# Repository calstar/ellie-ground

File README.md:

# ellie-ground
2022 Eillie Hot-fire Electronics Control

## Summary
**DAQboard.ino** file commands the ESP32 that reads data from sensors and commands from the COM Board, and sends data in a package to the COM Board.

**COMBoard.ino** file commands the ESP32 that receives data in a package from the DAQ  Board, sends commands to the DAQ Board, and sends data to MATLAB for plotting and data-saving purposes through the serial port.

**liveplot.m** is a MATLAB file that can receive data from the COM Board, create live plots, and save the data.
  1. **Change the test file name according to the trial number in the liveplot.m file.**
  2. Click "Run" to start the code, and close the plotting window to stop the code. Test data will be automatically stored in a spreadsheet under a folder called "**Test_Data_yyyy-mm-dd**."

## ESP32 MAC Addresses
- DAQ Breadboard:{0x24, 0x62, 0xAB, 0xD2, 0x85, 0xDC}
- COM Breadboard:{0xC4, 0xDD, 0x57, 0x9E, 0x91, 0x6C};
- DAQ Protoboard:

## ESP32 Pinouts (Updated 4/6)
-DAQ Breadboard:

## Software requirement
**Ctrl click (Windows) or Cmd click the following links to open them in new tabs**
1. Arduino (https://www.arduino.cc/en/software)
2. MATLAB (https://software.berkeley.edu/matlab®)
    - To control the serial port, you need to install the [**Instrument Control Toolbox**](https://www.mathworks.com/products/instrument.html).
3. (optional) An external code editing software such as Atom (https://atom.io) or Visual Studio (https://visualstudio.microsoft.com/downloads/).
    - Arduino IDE and MATLAB are sufficient for all the coding
4. (recommended) GitHub Desktop (https://desktop.github.com). You can pull, push, and edit files with ease. **Step 3 required if you would like to download GitHub Desktop as the software requires an external editor.**

## How to update
### Using Github Desktop
1. Make sure you have access to this project
    - Check with you administrators
2. Go to the Github app, sign in, and click on the top left corner. You should see a pop-up window with an "Add" button. Select that button and choose "Clone repository."
3. Search in "Filter you repositories" using the keyword "ellie-ground." Select the correct repository and click "Clone."
    - If you want this cloned repository to be in a different folder, change the "Local Path."
4. After you have edited and saved the file in the local repository, GitHub Desktop will detect changes and prompt you to commit. Make sure to double check your changes before committing.
5. On the bottom left corner, put down a short summary that describes what you have changed, then click "Commit to **main**."
6. In the middle of the screen (or on the top banner) you will see "Push commits to the origin remote." If you are sure that the commit is ready, click "Push origin."
6. Check the project online and see if the changes have been reflected.

### Using Git
Please refer to https://rocketry.gitbook.io/public/tutorials/avionics/git-and-workflow for more information.

## Helpful resources
### ESP32-DevkitC (for PCB application - antenna sticks out of board)
Getting started

https://docs.espressif.com/projects/esp-idf/en/latest/esp32/hw-reference/esp32/get-started-devkitc.html

Pinout reference

### ESP32-WROOM (for breadboard/protoboard application - antenna does NOT stick out of board)

Pinout reference

### ESP32-HUZZAH (for breadboard/protoboard application)

Pinout reference

### Pressure transducer color code
Red - E+

Black - E-

Green - A-

White - A+

Other possible combinations: Blue E+; Red E-; Green A-; Black A+

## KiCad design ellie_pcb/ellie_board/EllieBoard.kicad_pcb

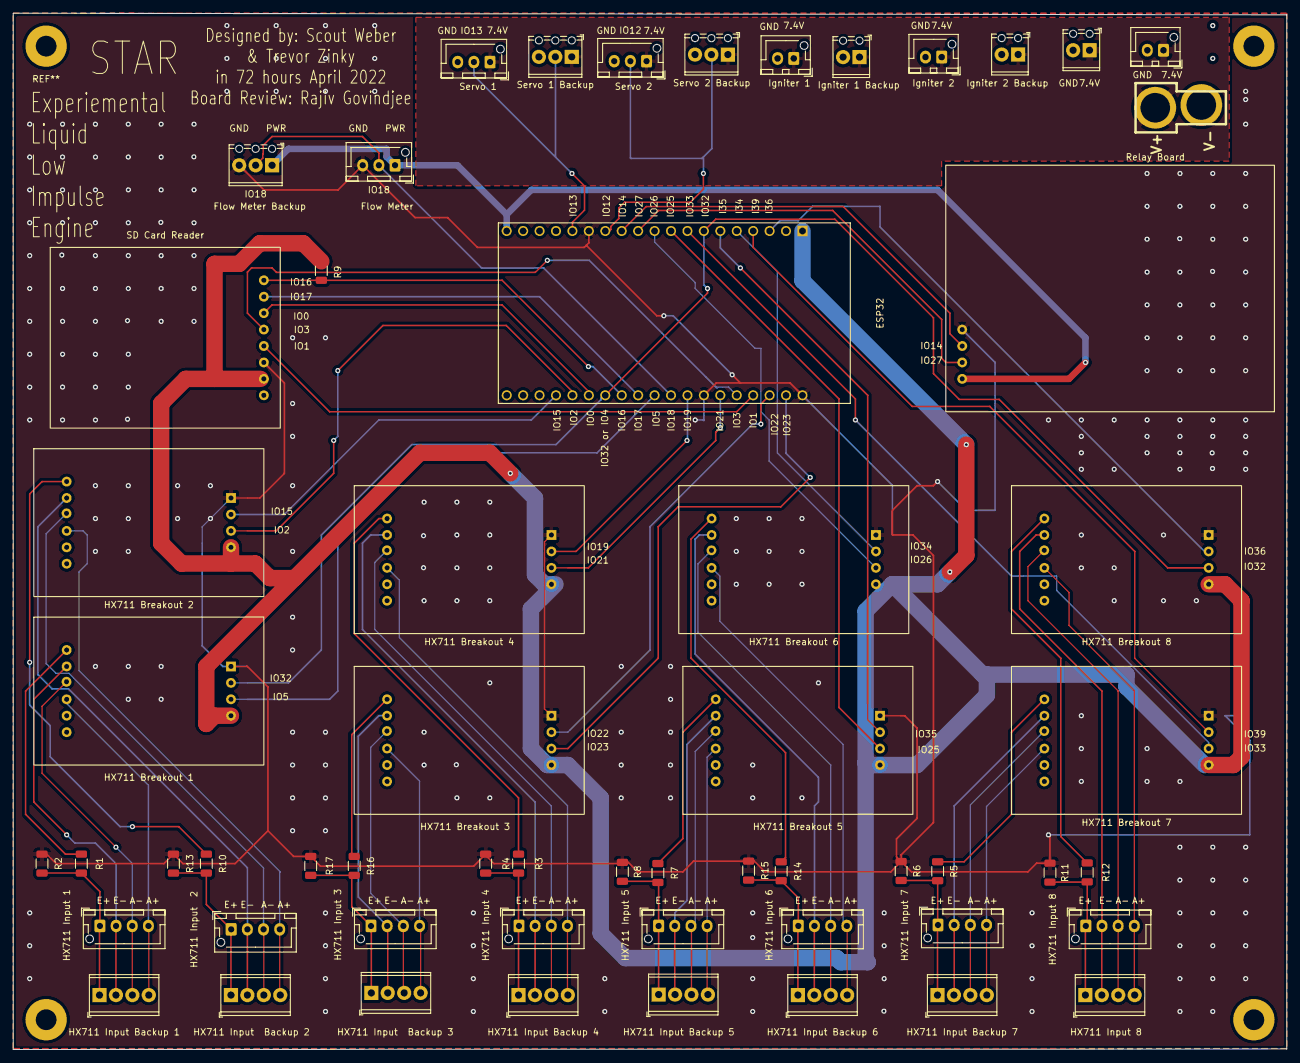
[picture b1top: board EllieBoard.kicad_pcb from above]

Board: 2 copper layers, 196.8 x 160.2 mm, 57 parts (0 on the bottom side), 69 nets.

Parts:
ESP32: ESP32-DEVKITC-32D; MODULE_ESP32-DEVKITC-32D
Flow Meter : Flow Meter Conn 1; JST_XH_B3B-XH-AM_1x03_P2.50mm_Vertical
Flow Meter Backup: Flow Meter Conn 2; TerminalBlock_Phoenix_MPT-0,5-3-2.54_1x03_P2.54mm_Horizontal
HX711 Breakout 1: HX711 Breakout 5; HX711_Breakout_Board
HX711 Breakout 2, HX711 Breakout 4, HX711 Breakout 6, HX711 Breakout 8: HX711_Breakout; HX711_Breakout_Board
HX711 Breakout 3: HX711 Breakout 6; HX711_Breakout_Board
HX711 Breakout 5: HX711 Breakout 7; HX711_Breakout_Board
HX711 Breakout 7: HX711 Breakout 8; HX711_Breakout_Board
HX711 Input 1: Load Cell 1.1; JST_XH_B4B-XH-AM_1x04_P2.50mm_Vertical
HX711 Input 3: Load Cell 3.1; JST_XH_B4B-XH-AM_1x04_P2.50mm_Vertical
HX711 Input 4: Load Cell 4.1; JST_XH_B4B-XH-AM_1x04_P2.50mm_Vertical
HX711 Input 5: Load Cell 5.1; JST_XH_B4B-XH-AM_1x04_P2.50mm_Vertical
HX711 Input 6: Load Cell 6.1; JST_XH_B4B-XH-AM_1x04_P2.50mm_Vertical
HX711 Input 7: Load Cell 7.1; JST_XH_B4B-XH-AM_1x04_P2.50mm_Vertical
HX711 Input 8: Load Cell 8.1; JST_XH_B4B-XH-AM_1x04_P2.50mm_Vertical
HX711 Input 8#2: Load Cell 8.2; TerminalBlock_Phoenix_MPT-0,5-4-2.54_1x04_P2.54mm_Horizontal
HX711 Input  2: Load Cell 2.1; JST_XH_B4B-XH-AM_1x04_P2.50mm_Vertical
HX711 Input  Backup 2: Load Cell 2.2; TerminalBlock_Phoenix_MPT-0,5-4-2.54_1x04_P2.54mm_Horizontal
HX711 Input  Backup 3: Load Cell 3.2; TerminalBlock_Phoenix_MPT-0,5-4-2.54_1x04_P2.54mm_Horizontal
HX711 Input Backup 1: Load Cell 1.2; TerminalBlock_Phoenix_MPT-0,5-4-2.54_1x04_P2.54mm_Horizontal
HX711 Input Backup 4: Load Cell 4.2; TerminalBlock_Phoenix_MPT-0,5-4-2.54_1x04_P2.54mm_Horizontal
HX711 Input Backup 5: Load Cell 5.2; TerminalBlock_Phoenix_MPT-0,5-4-2.54_1x04_P2.54mm_Horizontal
HX711 Input Backup 6: Load Cell 6.2; TerminalBlock_Phoenix_MPT-0,5-4-2.54_1x04_P2.54mm_Horizontal
HX711 Input Backup 7: Load Cell 7.2; TerminalBlock_Phoenix_MPT-0,5-4-2.54_1x04_P2.54mm_Horizontal
Igniter 1 , Igniter 2 : NC Conn; JST_XH_B2B-XH-AM_1x02_P2.50mm_Vertical
Igniter 1 Backup: Igniter 1; TerminalBlock_Phoenix_MPT-0,5-2-2.54_1x02_P2.54mm_Horizontal
Igniter 2 Backup: NC Conn 2; TerminalBlock_Phoenix_MPT-0,5-2-2.54_1x02_P2.54mm_Horizontal
J9: Battery Conn; DEANS
J10: Battery Conn Backup; JST_XH_B2B-XH-AM_1x02_P2.50mm_Vertical
J11: Battery Conn Backup 2; TerminalBlock_Phoenix_MPT-0,5-2-2.54_1x02_P2.54mm_Horizontal
R1, R3, R5, R7, R10, R12, R14, R16: 820; R_1206_3216Metric
R2, R4, R6, R8, R11, R13, R15, R17: 470; R_1206_3216Metric
R9: 10k; R_1206_3216Metric
Relay Board: Relay_Board; Relay_Breakout
SD Card Reader: SD_Card_Reader; SD_Card_Breakout
Servo 1 : Servo Conn 3; JST_XH_B3B-XH-AM_1x03_P2.50mm_Vertical
Servo 1 Backup: Servo Conn 4; TerminalBlock_Phoenix_MPT-0,5-3-2.54_1x03_P2.54mm_Horizontal
Servo 2 : Servo Conn 1; JST_XH_B3B-XH-AM_1x03_P2.50mm_Vertical
Servo 2 Backup: Servo Conn 2; TerminalBlock_Phoenix_MPT-0,5-3-2.54_1x03_P2.54mm_Horizontal

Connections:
+3V3: ESP32.1 (3V3), HX711 Breakout 1.10 (VCC), HX711 Breakout 2.10 (VCC), HX711 Breakout 3.10 (VCC), HX711 Breakout 4.10 (VCC), HX711 Breakout 5.10 (VCC), HX711 Breakout 6.10 (VCC), HX711 Breakout 7.10 (VCC), HX711 Breakout 8.10 (VCC), R9.1, SD Card Reader.7 (3V)
+5V: ESP32.19 (EXT_5V), Flow Meter.1, Flow Meter Backup.1, Relay Board.1 (VCC)
A1+: HX711 Breakout 1.4 (A+), HX711 Input 1.4, HX711 Input Backup 1.4
A1-: HX711 Breakout 1.3 (A-), HX711 Input 1.3, HX711 Input Backup 1.3
A2+: HX711 Breakout 2.4 (A+), HX711 Input 2.4, HX711 Input Backup 2.4
A2-: HX711 Breakout 2.3 (A-), HX711 Input 2.3, HX711 Input Backup 2.3
A3+: HX711 Breakout 3.4 (A+), HX711 Input 3.4, HX711 Input Backup 3.4
A3-: HX711 Breakout 3.3 (A-), HX711 Input 3.3, HX711 Input Backup 3.3
A4+: HX711 Breakout 4.4 (A+), HX711 Input 4.4, HX711 Input Backup 4.4
A4-: HX711 Breakout 4.3 (A-), HX711 Input 4.3, HX711 Input Backup 4.3
A5+: HX711 Breakout 5.4 (A+), HX711 Input 5.4, HX711 Input Backup 5.4
A5-: HX711 Breakout 5.3 (A-), HX711 Input 5.3, HX711 Input Backup 5.3
A6+: HX711 Breakout 6.4 (A+), HX711 Input 6.4, HX711 Input Backup 6.4
A6-: HX711 Breakout 6.3 (A-), HX711 Input 6.3, HX711 Input Backup 6.3
A7+: HX711 Breakout 7.4 (A+), HX711 Input 7.4, HX711 Input Backup 7.4
A7-: HX711 Breakout 7.3 (A-), HX711 Input 7.3, HX711 Input Backup 7.3
A8+: HX711 Breakout 8.4 (A+), HX711 Input 8.4, HX711 Input 8#2.4
A8-: HX711 Breakout 8.3 (A-), HX711 Input 8.3, HX711 Input 8#2.3
GND: ESP32.14 (GND1), ESP32.20 (GND3), ESP32.26 (GND2), Flow Meter.3, Flow Meter Backup.3, HX711 Breakout 1.7 (GND), HX711 Breakout 2.7 (GND), HX711 Breakout 3.7 (GND), HX711 Breakout 4.7 (GND), HX711 Breakout 5.7 (GND), HX711 Breakout 6.7 (GND), HX711 Breakout 7.7 (GND), HX711 Breakout 8.7 (GND), Igniter 1.2, Igniter 1 Backup.2, Igniter 2.2, Igniter 2 Backup.2, J9.2, J10.2, J11.2, R2.1, R4.1, R6.1, R8.1, R11.1, R13.1, R15.1, R17.1, Relay Board.4 (GND), SD Card Reader.6 (GND), Servo 1.3, Servo 1 Backup.3, Servo 2.3, Servo 2 Backup.3
IO2: ESP32.34 (IO2), HX711 Breakout 2.9 (SCK)
IO5: ESP32.29 (IO5), HX711 Breakout 1.9 (SCK)
IO12: ESP32.13 (IO12), Servo 2.2, Servo 2 Backup.2
IO13: ESP32.15 (IO13), Servo 1.2, Servo 1 Backup.2
IO14: ESP32.12 (IO14), Relay Board.3 (IN2)
IO15: ESP32.35 (IO15), HX711 Breakout 2.8 (DT)
IO16: ESP32.31 (IO16), R9.2, SD Card Reader.1 (CD)
IO17: ESP32.30 (IO17), SD Card Reader.2 (CS)
IO18: ESP32.28 (IO18), Flow Meter.2, Flow Meter Backup.2
IO19: ESP32.27 (IO19), HX711 Breakout 4.8 (DT)
IO21: ESP32.25 (IO21), HX711 Breakout 4.9 (SCK)
IO22: ESP32.22 (IO22), HX711 Breakout 3.8 (DT)
IO23: ESP32.21 (IO23), HX711 Breakout 3.9 (SCK)
IO25: ESP32.9 (IO25), HX711 Breakout 5.9 (SCK)
IO26: ESP32.10 (IO26), HX711 Breakout 6.9 (SCK)
IO27: ESP32.11 (IO27), Relay Board.2 (IN1)
IO32: ESP32.7 (IO32), ESP32.32 (IO4), HX711 Breakout 1.8 (DT), HX711 Breakout 8.9 (SCK)
IO33: ESP32.8 (IO33), HX711 Breakout 7.9 (SCK)
IO34: ESP32.5 (IO34), HX711 Breakout 6.8 (DT)
IO35: ESP32.6 (IO35), HX711 Breakout 5.8 (DT)
IO36: ESP32.3 (SENSOR_VP), HX711 Breakout 8.8 (DT)
IO39: ESP32.4 (SENSOR_VN), HX711 Breakout 7.8 (DT)
Lipo: Igniter 1.1, Igniter 1 Backup.1, Igniter 2.1, Igniter 2 Backup.1, J9.1, J10.1, J11.1, Servo 1.1, Servo 1 Backup.1, Servo 2.1, Servo 2 Backup.1
unnamed: HX711 Breakout 1.1 (E+), R1.2
unnamed: HX711 Breakout 4.1 (E+), R3.2
unnamed: HX711 Breakout 7.1 (E+), R5.2
unnamed: HX711 Breakout 5.1 (E+), R7.2
unnamed: HX711 Breakout 2.1 (E+), R10.2
unnamed: HX711 Breakout 8.1 (E+), R12.2
unnamed: HX711 Breakout 6.1 (E+), R14.2
unnamed: HX711 Breakout 3.1 (E+), R16.2
SCK/CLK: ESP32.23 (TXD0), SD Card Reader.5 (CK)
SDI/SD1: ESP32.33 (IO0), SD Card Reader.3 (DI)
SDO/SD0: ESP32.24 (RXD0), SD Card Reader.4 (DO)
out1: HX711 Input 1.1, HX711 Input Backup 1.1, R1.1, R2.2
out2: HX711 Input 2.1, HX711 Input Backup 2.1, R10.1, R13.2
out3: HX711 Input 3.1, HX711 Input Backup 3.1, R16.1, R17.2
out4: HX711 Input 4.1, HX711 Input Backup 4.1, R3.1, R4.2
out5: HX711 Input 5.1, HX711 Input Backup 5.1, R7.1, R8.2
out6: HX711 Input 6.1, HX711 Input Backup 6.1, R14.1, R15.2
out7: HX711 Input 7.1, HX711 Input Backup 7.1, R5.1, R6.2
out8: HX711 Input 8.1, HX711 Input 8#2.1, R11.2, R12.1
u1: HX711 Breakout 1.2 (E-), HX711 Input 1.2, HX711 Input Backup 1.2
u2: HX711 Breakout 2.2 (E-), HX711 Input 2.2, HX711 Input Backup 2.2
u3: HX711 Breakout 3.2 (E-), HX711 Input 3.2, HX711 Input Backup 3.2
u4: HX711 Breakout 4.2 (E-), HX711 Input 4.2, HX711 Input Backup 4.2
u5: HX711 Breakout 5.2 (E-), HX711 Input 5.2, HX711 Input Backup 5.2
u6: HX711 Breakout 6.2 (E-), HX711 Input 6.2, HX711 Input Backup 6.2
u7: HX711 Breakout 7.2 (E-), HX711 Input 7.2, HX711 Input Backup 7.2
u8: HX711 Breakout 8.2 (E-), HX711 Input 8.2, HX711 Input 8#2.2

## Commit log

2022-04-03 Apr 2 Edition
    First upload to ellie-ground project
2022-04-03 Apr 2 Edition
    First Upload
2022-04-03 added sending command back to COM Board
2022-04-03 extra comment
2022-04-04 adding sensor board schematic
2022-04-04 Update on test data and com daq code
2022-04-04 Adding layout for sensor board
2022-04-04 Adding schematic for sensor board
2022-04-04 custom board
2022-04-05 fixing some issues with schematic
2022-04-05 Add files via upload
    Working code as of sunday 4/3 build day
2022-04-05 Revert "Add files via upload"
    This reverts commit e99c1198ff01b9ae491ee7c082d96d64acfec7d3.
2022-04-05 Revert "Revert "Add files via upload""
    This reverts commit 7839cd9de83ff867efd8fdbad404a527c5cbbfa3.
2022-04-05 FM Calibration Code
    Created flowmeter calibration code and fixed existing flowmeter code in DAQ
2022-04-05 liveplot.m can now automatically store data
2022-04-05 Updated code 1 AM 4/5
    Finalized FM calibration code and DAQ code
2022-04-05 updated board electronics work session 04/04
2022-04-05 updated schematic electronics work session 04/05
2022-04-05 kicad board work
    custom board updates
2022-04-05 Update on ESP 32 DevkitC recourses
2022-04-05 Update on ESP32 reference materials
2022-04-05 some updates to layout, not 100% done yet
2022-04-05 Updated layout for review
2022-04-05 Updated layout for board, added silkscreen
2022-04-06 flow meter calibration changes before testing
2022-04-06 fm calibration during testing
2022-04-06 Layout updates 04/05
2022-04-06 start of flow testing
2022-04-06 Layout changes 04/05
2022-04-06 adding power pours + other misc edits
2022-04-06 matlab code push for hubetr
2022-04-06 mid fm calibration
2022-04-06 flow meter
2022-04-06 practice data sets
2022-04-06 data from fm calibration
2022-04-06 new liveplot
2022-04-06 Read Table
2022-04-06 Fixed power pour, added more silkscreen labels, attempted to make board less massive
2022-04-06 3 Codes on Reading Data
2022-04-06 last few edits to layout
2022-04-06 matlab plotting code
2022-04-06 adding vias fixing solder mask
2022-04-06 fixing net issues
2022-04-06 PCB Added silkscreen and final review from Trevor
2022-04-06 Kicad board connector and silkscreen fixes
2022-04-07 Working DAQ & COM Board before GOX testing
2022-04-07 gox flow testing data
2022-04-09 gox flow testing matlab code
2022-04-10 changes 4/9
2022-04-10 dev version of com board
2022-04-10 daq board to dev
2022-04-10 State machine
    Implementation of the state machine in the COMBoard code
2022-04-10 State Machine Updates
    COM and DAQ updates
2022-04-10 daq and com updates
2022-04-10 Working COM state machine (full)
    It works :)
2022-04-10 Updates
    Updates
2022-04-10 Matlab compatibility
2022-04-11 small dev board changes
2022-04-11 matlab
2022-04-11 matlab with data passing error
2022-04-11 flkh
    aejklh
2022-04-11 Revert "tt"
    This reverts commit 54d455385d4b6d7aa855cfb8e0c930104250ae1c.
2022-04-12 Fixed issues with live plot
    2 issues fixed:
    1. COM unable to interface with liveplot (set up functions to catch no reading case)
    2. change the fscaf() timeout time, so the program will only take between 0.75 (with reading no timeout) to 2 (without reading timeout) seconds to get ready
2022-04-12 COM board code LED update
    Now LED can display the states. Problem with shutting off matlab code modifies state to 0 remains. the issue is that MATLAB fclose, clear, instrreset functions would reset the esp32, therefore resett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
2022-04-13 Fire Sequence
    Implemented fire sequence
2022-04-13 Updated COM
2022-04-13 PT color code
2022-04-13 Testing code updates
2022-04-13 Revert "Merge branch 'main' of https://github.com/calstar/ellie-ground"
    This reverts commit 19382aaf51256c20d619034d2db27a935fc07c62, reversing
    changes made to 4dbdb6cad9a543b6ff85faa7afed69d0076f4346.
2022-04-13 Enabled LEDs
    LEDs
2022-04-13 Revert "Merge branch 'main' of https://github.com/calstar/ellie-ground"
    This reverts commit fc31e91a51d2958665cf79de26ba3b0561605e51, reversing
    changes made to fb18d1940c5d94178e9e6579c36cea799c117d0d.
2022-04-13 Revert "Revert "Merge branch 'main' of https://github.com/calstar/ellie-ground""
    This reverts commit ee03be48f70488f3a0436184d735dd6d9fed3472.
2022-04-13 Updated Testing
    Yay :)
2022-04-13 daq code updates 4/12
2022-04-14 pt test code
2022-04-14 Transfer working code to main
2022-04-14 Attempted Fix
2022-04-14 sd card tirals
2022-04-14 Hardware fix
2022-04-15 COM updates
2022-04-15 com input board testing code
2022-04-16 com interface test
2022-04-16 archiving old code
2022-04-16 Modified COM
2022-04-16 Updated DAQ
2022-04-16 dylan daq setup
2022-04-16 COM Update
2022-04-16 Liveplot NEW
2022-04-16 Final code changes
2022-04-16 Fix for dead zone
2022-04-16 Renaming
2022-04-25 Left over commit
2022-04-25 Resting power draw fix
2022-04-25 Reduce igniter power draw
2022-04-28 added code to measure voltage
2022-05-01 (test) measure from voltage divider
2022-05-07 PT Gauge cal data from FAR
2022-05-07 Re-organization
2022-05-13 may12work session
2022-05-13 update may12 last
2022-05-13 matlab update
2022-05-13 Error Handling Update
2022-05-14 Changed load cell to PT
2022-05-14 SD card Update
2022-05-17 may 16 daq plus other updates
2022-05-17 voltage sensing code
2022-05-17 updated relay test
2022-05-17 COM DAQ Update
2022-05-17 May17Update
2022-05-18 COM DAQ working code
2022-05-18 labview com board start
2022-05-18 added stable code
2022-05-19 Main Update
2022-05-19 new DAQ code WIP
2022-05-19 main com
2022-05-19 update daq
2022-05-19 random matlab stuff
2022-05-19 updated DAQ code
    Rewrote the whole code to make it better
2022-05-19 moved daq board dev to different folder
2022-05-20 COM NOT WORK
2022-05-20 Redone COM DEV board
2022-05-20 COM and DAQ updates, should be stable
2022-05-21 MATLAB plotting Fix
2022-05-21 emergency tracking code for irec/jenya
2022-05-21 big DevDAQ and DevCOM changes hotfire eve
2022-05-21 matlavb
2022-05-21 hotfire changes
2022-05-21 matlab divide by 100
2022-05-22 Everything
2022-05-23 FAR Hotfire changes and MATAB data analysis
2022-06-02 Processed Hot Fire Data
2022-06-15 DataAnalysis update
2022-06-28 Mass flow meter
2022-06-28 Change file path
2022-08-25 added kicad files
2022-08-26 new pcb
2022-08-27 Testing Commit
2022-08-27 Created dedicated LE2 DAQ and COM
2022-08-27 Updated file names
2022-08-27 moving files
2022-08-27 Initial DAQ changes
2022-08-29 new FM code
2022-08-29 new fm
2022-08-29 labview updates
2022-09-01 WORKING(ISH) FM CODE
2022-09-01 fm??
2022-09-01 FM: can return pulse length (period)
2022-09-01 FM: records pulse length (period)
2022-09-02 FM DUBS
2022-09-03 Sensor Code Ready For Calibration
2022-09-10 working version 09/10
2022-09-24 Update on CD calculation
2022-09-25 Sep24 builday final
2022-09-25 Deletion of files
2022-09-25 Rename folders
2022-09-27 Ds Store
2022-09-27 labview tutorial code
2022-10-04 flow Meter fixed
2022-10-06 misc
2022-10-06 added new fm code
2022-10-06 no csv capability
2022-10-06 csv yeehawwwww
2022-10-06 delete
2022-10-06 new new new fm code
2022-10-06 blep
2022-10-06 NEW FM FR NOW
2022-10-15 Pressurization Sequence
    Added capability for pressurization and QDs. See user guide in software section of drive for more details
2022-10-29 Created servoTest
2022-11-02 test
    test
2022-11-04 Pressure Code Reviewed
2022-11-05 Modified Pressure Filling to estimate overshoot
2022-11-24 rtd w/ wheatstone bridge code
2022-12-18 math :(
2023-04-10 revert to original hotfire
